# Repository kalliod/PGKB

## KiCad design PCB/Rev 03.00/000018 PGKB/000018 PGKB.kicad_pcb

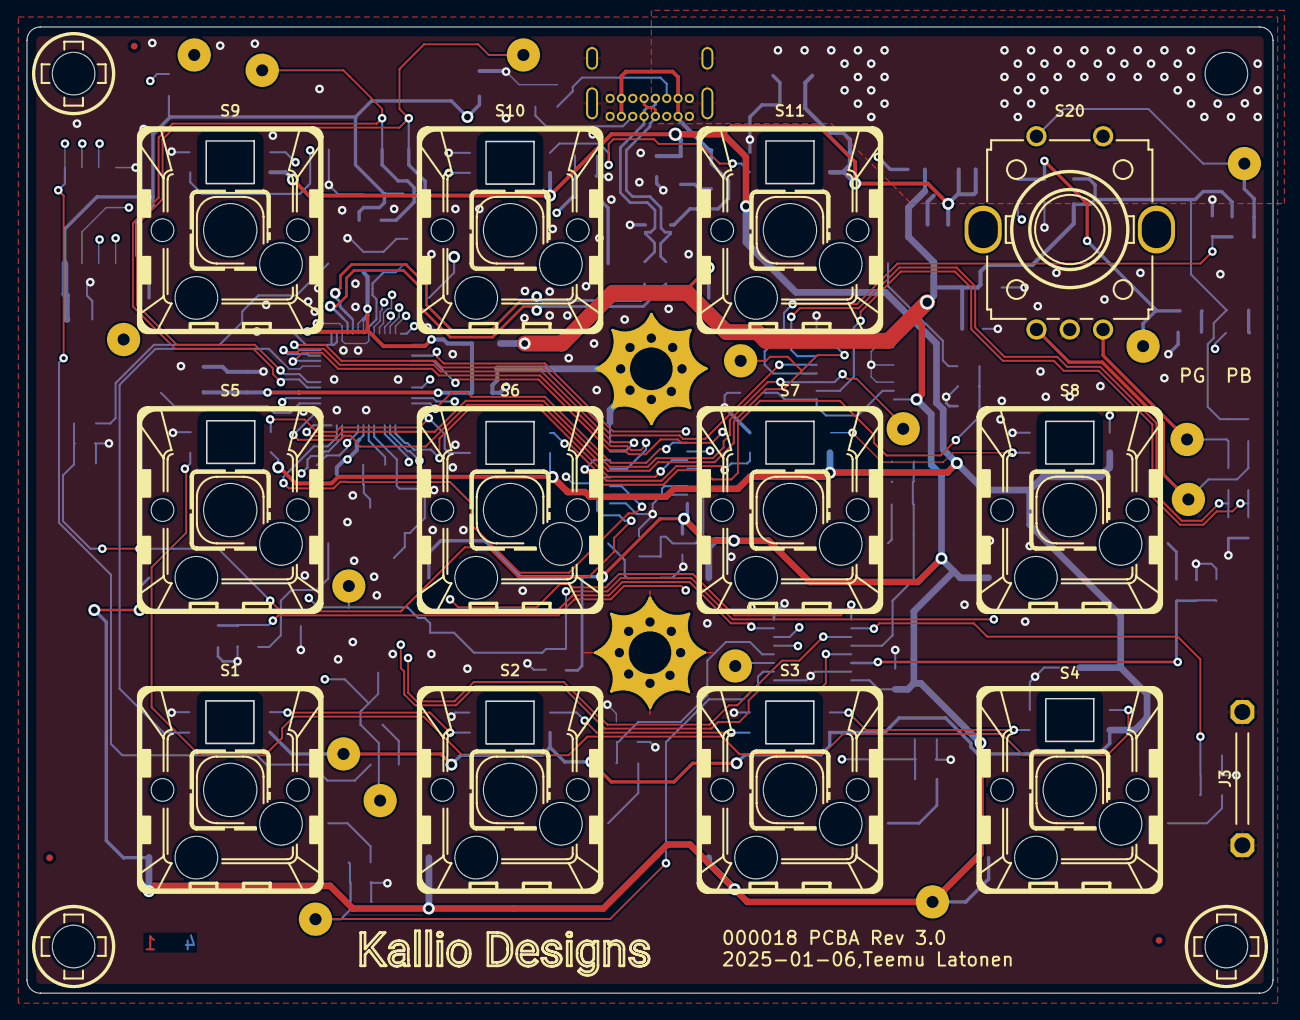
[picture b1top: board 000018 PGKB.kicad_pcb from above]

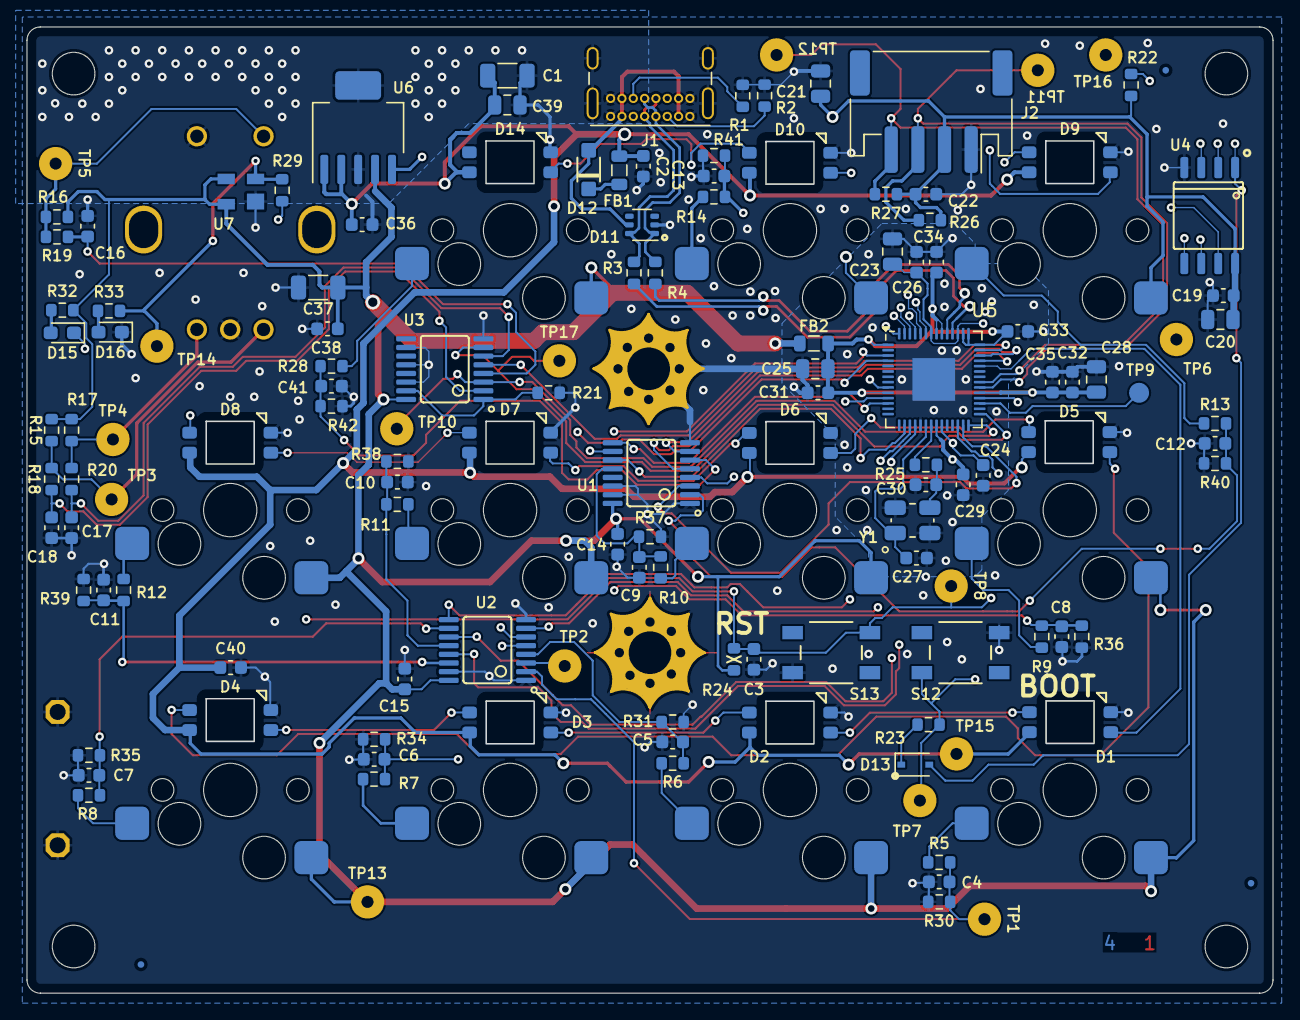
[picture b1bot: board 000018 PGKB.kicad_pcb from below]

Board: 4 copper layers, 93.5 x 72.5 mm, 157 parts (133 on the bottom side), 86 nets.

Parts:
ART1: 4-Layer Marking; ART_4-LAYER
ART2: Logo 2.5 mm Silk; ART_LOGO_TEXT_2.5MM_SILK
C1, C37: 10u; CAPC3216X150N
C2, C14, C15, C16, C17, C18, C19, C22, C24, C26, C29, C31, C32, C33, C34, C35, C36, C38, C40: 100n; CAPC1608X90N
C3, C4, C5, C6, C7, C8, C9, C10, C11, C12, C13, C41: 10n; CAPC1608X90N
C20, C21, C23, C25, C28, C39: 1u; CAPC2012X135N
C27, C30: 27p; CAPC1608X90N
D1, D2, D3, D4, D5, D6, D7, D8, D9, D10, D14: Neopixel Reverse; LEDM_NEO3535_REVERSE_SK6812-E
D11: DRTR5V0U4S-7; SOT-363_SC-70-6
D12: PMEG3010ER,115; DIOC360X180X150N_A
D13: BAT54WS; D_SOD-323
D15: Red; LEDM1608X70M
D16: Green; LEDM1608X70M
FB1, FB2: MMZ2012Y152BT000; INDC2016X100N
FD1, FD2, FD3, FD4, FD5, FD6: Fiducial 0.5 mm; Fiducial_0.5mm_Mask1mm
H1, H2, H4: NPTH 3.2 M3 Clearance; NPTH_3.2mm_M3_clearance
H3: NPTH_3.2; NPTH_3.2mm
H5, H6: PTH 3.2 M3 Clearance; PTH_3.2mm_M3_clearance_B
J1: USB C; USB_C_Receptacle_GCT_USB4085
J2: S4B-PH-SM4-TB; JST_PH_S4B-PH-SM4-TB_1x04-1MP_P2.00mm_Horizontal
J3: GND Hook; GND_HOOK_M
R1, R2, R26, R27: 5k1; RESC1608X55N
R3, R4: 27; RESC1608X55N
R5, R6, R7, R8, R9, R10, R11, R12, R13, R14, R15, R16, R17, R23, R25, R28: 1k; RESC1608X55N
R18, R19, R20, R21, R22, R29: 10k; RESC1608X55N
R24: DNP; RESC1608X55N_DNP
R30, R31, R34, R35, R36, R37, R38, R39, R40, R41, R42: 100k; RESC1608X55N
R32, R33: 360; RESC1608X55N
S1, S2, S3, S4, S5, S6, S7, S8, S9, S10, S11: 4958; SWITCH_BUTTON_Kailh_mx_socket
S12, S13: PTS647SN38SMTR2 LFS; SW_Push_1P1T_NO_CK_PTS647SN50SMTR2LFS
S20: PEC11R-4215K-S0012; RotaryEncoder_Bourns_Vertical_PEC11R-4x15f-Sxxxx
TP1, TP2, TP3, TP4, TP5, TP6, TP7, TP8, TP10, TP11, TP12, TP13, TP14, TP15, TP16, TP17: TP D2.5 mm H0.9mm; TestPoint_Pad_D2.5mm_H0.9mm
TP9: TestPoint_1.5mm_Round; TestPoint_Pad_D1.5mm
U1, U2, U3: SN74HCS365PWR; SOP65P600X150-16N
U4: W25Q80DVSSIG; SOIC127P790X195-8N
U5: RP2040; QFN-56-1EP_7x7mm_P0.4mm_EP3.2x3.2mm
U6: MCP1825T-3302E/DC; SOT127P700X180-6N
U7: CAT811TTBI-GT3; SOT-143_TO-253_M
Y1: 12 MHz; OSCCC320X250X70_M

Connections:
+3V3: C14.1, C15.1, C19.1, C20.1, C21.1, C22.1, C37.1, C38.1, FB2.1, J2.2, R15.1, R16.1, R17.1, R22.1, R24.2, R26.1, R27.1, R32.2, S1.1, S2.1, S3.1, S4.1, S5.1, S6.1, S7.1, S8.1, S9.1, S10.1, S11.1, TP13.1, U1.16 (VCC), U2.16 (VCC), U3.16 (VCC), U4.8 (VCC), U6.4 (VO), U7.3 (~MR), U7.4 (VCC)
/Main/Buttons/Button1: TP2.1, U2.3 (O1), U5.3 (GPIO1)
/Main/Buttons/Button2: U2.5 (O2), U5.4 (GPIO2)
/Main/Buttons/Button3: U2.7 (O3), U5.9 (GPIO7)
/Main/Buttons/Button4: U2.9 (O4), U5.11 (GPIO8)
/Main/Buttons/Button5: U1.9 (O4), U5.12 (GPIO9)
/Main/Buttons/Button6: U1.11 (O5), U5.16 (GPIO13)
/Main/Buttons/Button7: U2.11 (O5), U5.17 (GPIO14)
/Main/Buttons/Button8: U2.13 (O6), U5.18 (GPIO15)
/Main/Buttons/Button9: U1.3 (O1), U5.27 (GPIO16)
/Main/Buttons/Button10: U1.5 (O2), U5.39 (GPIO27_ADC1)
/Main/Buttons/Button11: U1.7 (O3), U5.40 (GPIO28_ADC2)
/Main/Connectors/I2C1_SCL: J2.4, R27.2, TP12.1, U5.35 (GPIO23)
/Main/Connectors/I2C1_SDA: J2.3, R26.2, TP11.1, U5.34 (GPIO22)
/Main/Memory/CLK: U4.6 (CLK), U5.52 (QSPI_SCLK)
/Main/Memory/DATA0: U4.5 (DI(IO0)), U5.53 (QSPI_SD0)
/Main/Memory/DATA1: U4.2 (DO(IO1)), U5.55 (QSPI_SD1)
/Main/Memory/DATA2: U4.3 (~WP(IO2)), U5.54 (QSPI_SD2)
/Main/Memory/DATA3: U4.7 (~HOLD(IO3)), U5.51 (QSPI_SD3)
/Main/Memory/~CS_MEMORY: D13.2 (A), R22.2, U4.1 (~CS), U5.56 (QSPI_SS)
/Main/Microcontroller/1V2: C23.1, C24.1, C26.1, TP6.1, U5.23 (DVDD), U5.45 (VREG_VOUT), U5.50 (DVDD)
/Main/Microcontroller/3V3_MCU: C25.1, C28.1, C29.1, C31.1, C32.1, C33.1, C34.1, C35.1, FB2.2, U5.1 (IOVDD), U5.10 (IOVDD), U5.22 (IOVDD), U5.33 (IOVDD), U5.42 (IOVDD), U5.43 (ADC_AVDD), U5.44 (VREG_IN), U5.48 (USB_VDD), U5.49 (IOVDD)
/Main/Microcontroller/ENC_A: TP10.1, U3.3 (O1), U5.28 (GPIO17)
/Main/Microcontroller/ENC_B: TP17.1, U3.7 (O3), U5.29 (GPIO18)
/Main/Microcontroller/GPIO29: U3.5 (O2), U5.41 (GPIO29_ADC3)
/Main/Microcontroller/NEOPIX_DRIVE: D1.4 (DIN), U5.38 (GPIO26_ADC0)
/Main/Microcontroller/TP10: TP9.1, U5.31 (GPIO20)
/Main/Microcontroller/USBBOOT: R23.2, S12.3, TP7.1, U5.32 (GPIO21)
/Main/Microcontroller/USB_MCU_D_N: R3.2, U5.46 (USB_DM)
/Main/Microcontroller/USB_MCU_D_P: R4.2, U5.47 (USB_DP)
/Main/Microcontroller/~RESET: C3.2, R24.1, R29.2, S13.3, TP8.1, U5.26 (RUN)
/Main/Neopixel LEDs/NEOPIXEL_VDD: C1.1, C2.1, C36.1, C39.1, C40.1, D1.1 (VDD), D2.1 (VDD), D3.1 (VDD), D4.1 (VDD), D5.1 (VDD), D6.1 (VDD), D7.1 (VDD), D8.1 (VDD), D9.1 (VDD), D10.1 (VDD), D14.1 (VDD), FB1.2, TP15.1, U6.1 (~SHDN), U6.2 (VI)
/Main/USB Connector/CC1: J1.A5 (CC1), R2.1
/Main/USB Connector/CC2: J1.B5 (CC2), R1.1
/Main/USB Connector/USB_D_N: D11.6, J1.A7 (D-), J1.B7 (D-), R3.1
/Main/USB Connector/USB_D_P: D11.1, J1.A6 (D+), J1.B6 (D+), R4.1
GND: C1.2, C2.2, C3.1, C4.2, C5.2, C6.2, C7.2, C8.2, C9.2, C10.2, C11.2, C12.2, C13.2, C14.2, C15.2, C16.1, C17.1, C18.1, C19.2, C20.2, C21.2, C22.2, C23.2, C24.2, C25.2, C26.2, C27.2, C28.2, C29.2, C30.2, C31.2, C32.2, C33.2, C34.2, C35.2, C36.2, C37.2, C38.2, C39.2, C40.2, C41.2, D1.3 (VSS), D2.3 (VSS), D3.3 (VSS), D4.3 (VSS), D5.3 (VSS), D6.3 (VSS), D7.3 (VSS), D8.3 (VSS), D9.3 (VSS), D10.3 (VSS), D11.2 (V-), D14.3 (VSS), D16.1 (K), H5.1, H6.1, J1.A1 (GND), J1.A12 (GND), J1.B1 (GND), J1.B12 (GND), J1.S1 (SHIELD), J2.1, J3.1, J3.2 (Pin_1), R1.2, R2.2, R21.1, R30.2, R31.2, R34.2, R35.2, R36.2, R37.2, R38.2, R39.2, R40.2, R41.2, R42.2, S12.2, S13.2, S20.C, S20.S2, U1.1 (E1), U1.8 (GND), U1.14 (I6), U1.15 (E2), U2.1 (E1), U2.8 (GND), U2.15 (E2), U3.8 (GND), U3.10 (I4), U3.12 (I5), U3.14 (I6), U4.4 (GND), U5.19 (TESTEN), U5.57 (GND), U6.3 (GND), U6.6 (GND), U7.1 (GND), Y1.2 (GND), Y1.4 (GND)
unnamed: C30.1, R25.1, Y1.3
unnamed: D1.2 (DOUT), D2.4 (DIN)
unnamed: D2.2 (DOUT), D3.4 (DIN)
unnamed: D3.2 (DOUT), D4.4 (DIN)
unnamed: D4.2 (DOUT), D5.4 (DIN)
unnamed: D5.2 (DOUT), D6.4 (DIN)
unnamed: D6.2 (DOUT), D7.4 (DIN)
unnamed: D7.2 (DOUT), D8.4 (DIN)
unnamed: D8.2 (DOUT), D9.4 (DIN)
unnamed: D9.2 (DOUT), D10.4 (DIN), TP16.1
unnamed: D10.2 (DOUT), D14.4 (DIN)
unnamed: D11.5 (V+), D12.2 (A), J1.A4 (VBUS), J1.A9 (VBUS), J1.B4 (VBUS), J1.B9 (VBUS)
unnamed: D12.1 (K), FB1.1
unnamed: D13.1 (K), R23.1
unnamed: D15.2 (A), R32.1
unnamed: D15.1 (K), U6.5 (PG)
unnamed: D16.2 (A), R33.1
unnamed: R5.1, S1.2
unnamed: R6.1, S2.2
unnamed: R7.1, S3.2
unnamed: R8.1, S4.2
unnamed: R9.1, S5.2
unnamed: R10.1, S6.2
unnamed: R11.1, S7.2
unnamed: R12.1, S8.2
unnamed: R13.1, S9.2
unnamed: R14.1, S10.2
unnamed: R15.2, R18.1, S20.A, TP3.1
unnamed: R16.2, R19.1, S20.S1, TP5.1
unnamed: R17.2, R20.1, S20.B, TP4.1
unnamed: R28.1, S11.2
unnamed: C12.1, R13.2, R40.1, U1.2 (I1)
unnamed: C13.1, R14.2, R41.1, U1.4 (I2)
unnamed: C41.1, R28.2, R42.1, U1.6 (I3)
unnamed: C8.1, R9.2, R36.1, U1.10 (I4)
unnamed: C9.1, R10.2, R37.1, U1.12 (I5)
unnamed: C4.1, R5.2, R30.1, TP1.1, U2.2 (I1)
unnamed: C5.1, R6.2, R31.1, U2.4 (I2)
unnamed: C6.1, R7.2, R34.1, U2.6 (I3)
unnamed: C7.1, R8.2, R35.1, U2.10 (I4)
unnamed: C10.1, R11.2, R38.1, U2.12 (I5)
unnamed: C11.1, R12.2, R39.1, U2.14 (I6)
unnamed: R21.2, U3.1 (E1), U3.15 (E2)
unnamed: C18.2, R18.2, U3.2 (I1)
unnamed: C16.2, R19.2, U3.4 (I2)
unnamed: C17.2, R20.2, U3.6 (I3)
unnamed: C27.1, U5.20 (XIN), Y1.1
unnamed: R25.2, U5.21 (XOUT)
PERIP_~RESET: R29.1, R33.2, TP14.1, U7.2 (RST)

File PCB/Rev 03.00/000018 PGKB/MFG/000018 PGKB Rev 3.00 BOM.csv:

Reference,Value,Datasheet,Qty,DNP,DNP,MFG_PartNo,Manufacturer,Supplier,Supplier_PartNo
"C1,C37",10u,https://www.samsungsem.com/kr/support/product-search/mlcc/CL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,2,F,F,CL31B106MOHNNNE,Samsung Electro-Mechanics,Digi-Key,1276-6641-1-ND
"C2,C14,C15,C16,C17,C18,C19,C22,C24,C26,C29,C31,C32,C33,C34,C35,C36,C38,C40",100n,https://mm.digikey.com/Volume0/opasdata/d220001/medias/docus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,19,F,F,CL10B104KB8NNWC,Samsung,Digi-Key,1276-1935-1-ND
"C3,C4,C5,C6,C7,C8,C9,C10,C11,C12,C13,C41",10n,https://product.tdk.com/en/system/files?file=dam/doc/product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,12,F,F,C1608X7R2A103K080AA,TDK Corporation,Digi-Key,445-1304-1-ND
"C20,C21,C23,C25,C28,C39",1u,https://mm.digikey.com/Volume0/opasdata/d220001/medias/docus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,6,F,F,CL21B105KAFNNNE,Samsung Electro-Mechanics,Digi-Key,1276-1066-1-ND
"C27,C30",27p,http://www.passivecomponent.com/wp-content/uploads/datasheet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,2,F,F,0603N270J500CT,Walsin Technology Corporation,Digi-Key,1292-1511-1-ND
"D1,D2,D3,D4,D5,D6,D7,D8,D9,D10,D14",Neopixel Reverse,https://cdn-shop.adafruit.com/product-files/4960/4960_SK6812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,11,F,F,4960,Adafruit Industries LLC,Digi-Key,1528-4960-ND
D11,TVS_5V5_DRTR5V0U4S-7-M,https://www.diodes.com/assets/Datasheets/DRTR5V0U4S.pdf,1,F,F,DRTR5V0U4S-7,Diodes Incorporated,Digi-Key,DRTR5V0U4S-7DICT-ND
D12,Schottky_30V_1A_PMEG3010ER_115,https://assets.nexperia.com/documents/data-sheet/PMEG3010ER.pdf,1,F,F,"PMEG3010ER,115",Nexperia USA Inc.,Digi-Key,1727-5201-1-ND
D13,Schottky_30V_200mA_DCo_BAT54WS,https://diotec.com/tl_files/diotec/files/pdf/datasheets/bat54ws.pdf,1,F,F,BAT54WS,DComponents,Digi-Key,2721-BAT54WSTR-ND
D15,Red,https://mm.digikey.com/Volume0/opasdata/d220001/medias/docus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,1,F,F,B1911USD-20D000114U1930,Harvatek Corporation,Digi-Key,3147-B1911USD-20D000114U1930CT-ND
D16,Green,https://mm.digikey.com/Volume0/opasdata/d220001/medias/docus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,1,F,F,B1911NG--20D000214U1930,Harvatek Corporation,Digi-Key,3147-B1911NG--20D000214U1930CT-ND
"FB1,FB2",MMZ2012Y152BT000,https://product.tdk.com/en/system/files?file=dam/doc/product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,2,F,F,MMZ2012Y152BT000,Abracon LLC,Digi-Key,445-MMZ2012Y152BT000CT-ND
"H1,H2,H4",NPTH 3.2 M3 Clearance,,3,T,T,DNP,DNP,DNP,DNP
H3,NPTH_3.2,,1,T,T,DNP,DNP,DNP,DNP
"H5,H6",PTH 3.2 M3 Clearance,,2,T,T,DNP,DNP,DNP,DNP
J1,USB C,https://gct.co/files/drawings/usb4085.pdf,1,F,F,USB4085-GF-A,GCT,Digi-Key,2073-USB4085-GF-ACT-ND
J2,S4B-PH-SM4-TB,https://www.jst-mfg.com/product/pdf/eng/ePH.pdf,1,F,F,S4B-PH-SM4-TB,JST Sales America Inc.,Digi-Key,455-S4B-PH-SM4-TBCT-ND
J3,GND Hook,,1,T,T,DNP,DNP,DNP,DNP
"R1,R2,R26,R27",R_0603_5100_1%,https://www.seielect.com/catalog/sei-rmcf_rmcp.pdf,4,F,F,RMCF0603JT5K10,Stackpole Electronics Inc,Digi-Key,RMCF0603JT5K10CT-ND
"R3,R4",27,https://www.bourns.com/docs/product-datasheets/cr.pdf?sfvrsn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,2,F,F,CR0603-FX-27R0ELF,Bourns Inc.,Digi-Key,CR0603-FX-27R0ELFCT-ND
"R5,R6,R7,R8,R9,R10,R11,R12,R13,R14,R15,R16,R17,R23,R25,R28",1k,https://www.seielect.com/Catalog/SEI-RMCF_RMCP.pdf,16,F,F,RMCF0603JT1K00,Stackpole Electronics Inc,Digi-Key,RMCF0603JT1K00CT-ND
"R18,R19,R20,R21,R22,R29",10k,https://www.seielect.com/Catalog/SEI-RMCF_RMCP.pdf,6,F,F,RMCF0603FT10K0,Stackpole Electronics Inc,Digi-Key,RMCF0603FT10K0CT-ND
R24,R_0603_DNP,,1,T,T,DNP,DNP,DNP,DNP
"R30,R31,R34,R35,R36,R37,R38,R39,R40,R41,R42",100k,https://www.seielect.com/catalog/sei-rmcf_rmcp.pdf,11,F,F,RMCF0603FT100K,Stackpole Electronics Inc,Digi-Key,RMCF0603FT100KCT-ND
"R32,R33",360,https://www.yageo.com/upload/media/product/productsearch/dat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,2,F,F,RT0603FRE07360RL,YAGEO,Digi-Key,13-RT0603FRE07360RLCT-ND
"S1,S2,S3,S4,S5,S6,S7,S8,S9,S10,S11",4958,https://mm.digikey.com/Volume0/opasdata/d220001/medias/docus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,11,F,F,4958,Adafruit,Digi-Key,1528-4958-ND
"S12,S13",4.30181E+11,https://www.mouser.fi/datasheet/2/445/430181038816-1717160.pdf,2,F,F,4.30181E+11,Wurth Elektronik,Mouser,710-430181038816
S20,PEC11R-4215K-S0012,https://www.bourns.com/docs/Product-Datasheets/PEC11R.pdf,1,F,F,PEC11R-4215K-S0012,Bourns Inc.,Digi-Key,PEC11R-4215K-S0012-ND
"TP1,TP2,TP3,TP4,TP5,TP6,TP7,TP8,TP10,TP11,TP12,TP13,TP14,TP15,TP16,TP17",TP D2.5 mm H0.9mm,DNP,16,T,T,DNP,DNP,DNP,DNP
TP9,TestPoint_1.5mm_Round,DNP,1,T,T,DNP,DNP,DNP,DNP
"U1,U2,U3",SN74HCS365PWR,https://www.ti.com/lit/ds/symlink/sn74hcs365.pdf,3,F,F,SN74HCS365PWR,Texas Instruments,Digi-Key,296-SN74HCS365PWRCT-ND
U4,W25Q80DVSSIG,https://www.winbond.com/resource-files/w25q80dv%20dl_revh_10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,1,F,F,W25Q80DVSSIG,Winbond Electronics,Digi-Key,W25Q80DVSSIG-ND
U5,RP2040,https://datasheets.raspberrypi.com/rp2040/rp2040-datasheet.pdf,1,F,F,SC0914(13),Raspberry Pi,Digi-Key,2648-SC0914(13)CT-ND
U6,MCP1825T-3302E/DC,https://ww1.microchip.com/downloads/en/DeviceDoc/22056b.pdf,1,F,F,MCP1825T-3302E/DC,Microchip Technology,Digi-Key,MCP1825T-3302E/DCCT-ND
U7,CAT811TTBI-GT3,https://www.onsemi.com/pdf/datasheet/cat811-d.pdf,1,F,F,CAT811TTBI-GT3,onsemi,Digi-Key,CAT811TTBI-GT3OSCT-ND
Y1,12 MHz,https://www.mouser.fi/datasheet/2/3/ABM8_272_T3-3392615.pdf,1,F,F,ABM8-272-T3,Abracon LLC,Digi-Key,535-ABM8-272-T3CT-ND

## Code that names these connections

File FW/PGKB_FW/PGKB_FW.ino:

#include <Wire.h>
#include "Adafruit_MCP23017.h"
#include "KD_ardu_button.h"
#include <Keyboard.h>

/* Hardware configuration */

// TL: My keyboard writes 900 characters if a key is pressed for 30 sec. If
// two keys are pressed the amount of characters is doubled

// HW
#define BUTTON_DEBOUNCE 20                          // button debounce (ms)
#define NO_OF_BUTTONS 8

// ADC
#define AUX_VREF 2.56
#define ADC_CHANNELS 1024

/* Define debugging level */

// Doesn't work too well with serial port and HID enabled
#define DEBUG_LEVEL 0
#define POST_INTERVAL 5000

/* Serial port */

#define SERIAL_BAUD_RATE 57600                      // 57600 max with internal 8 MHz oscillator

/* Keyboard layout */

#define KB_LAYOUT_FI

/***********************************************************************************************************************/
/*                                                  pin definitions                                                    */
/***********************************************************************************************************************/

/* Arduino digital */
const int button1_pin = 12;
const int button2_pin = 6;
const int button3_pin = 8;
const int button4_pin = 0;   // NOT CONNECTED IN PCB REV 1.00
const int button5_pin = 9;
const int button6_pin = 10;
const int button7_pin = 11;
const int button8_pin = 13;

const int interrupt7_pin = 7;

//const int rx_led_pin = ??; // ARE THESE HW FUNCTIONS?
//const int tx_led_pin = 4;

/* Arduino analog */
const int analog0 = 14;
const int analog1 = 15;
//const int analog2 = 16;     // NOT IN USE
//const int analog3 = 17;     // NOT IN USE
const int analog4 = 18;
const int analog5 = 19;
//const int analog6 = 20;     // WHICH PIN?
//const int analog7 = 21;     // WHICH PIN?

/***********************************************************************************************************************/
/*                                                   VARIABLES                                                         */
/***********************************************************************************************************************/

/* Other variables */

// pin, pullup, inverted
Button onb_button[NO_OF_BUTTONS];

// Debugging
unsigned long _last_post_time = 0;
byte cycle_count = 0;

// Keyboard
bool b_pressed[NO_OF_BUTTONS];
char b_char[NO_OF_BUTTONS][2];

/***********************************************************************************************************************/
/*                                                   FUNCTIONS                                                         */
/***********************************************************************************************************************/

/* Analog in */
float read_voltage();

/***********************************************************************************************************************/
/*                                                   SETUP LOOP                                                        */
/***********************************************************************************************************************/

void setup() {

/* Keyboard layout */
// compare to US Apple Macintosh keyboard layout

#ifdef KB_LAYOUT_US
  b_char[0][0] = '\0';
  b_char[0][1] = ')';
  b_char[1][0] = '\0';
  b_char[1][1] = '(';
  b_char[2][0] = '\0';
  b_char[2][1] = '}';
  b_char[3][0] = '\0';
  b_char[3][1] = '{';
  b_char[4][0] = '\0';
  b_char[4][1] = ']';
  b_char[5][0] = '\0';
  b_char[5][1] = '[';
  b_char[6][0] = '\0';
  b_char[6][1] = '"';
  b_char[7][0] = '\0';
  b_char[7][1] = '\'';
#endif

#ifdef KB_LAYOUT_FI
  b_char[0][0] = KEY_LEFT_SHIFT;
  b_char[0][1] = '9';
  b_char[1][0] = KEY_LEFT_SHIFT;
  b_char[1][1] = '8';
  b_char[2][0] = KEY_RIGHT_ALT;
  b_char[2][1] = '0';
  b_char[3][0] = KEY_RIGHT_ALT;
  b_char[3][1] = '7';
  b_char[4][0] = KEY_RIGHT_ALT;
  b_char[4][1] = '9';
  b_char[5][0] = KEY_RIGHT_ALT;
  b_char[5][1] = '8';
  b_char[6][0] = KEY_LEFT_SHIFT;
  b_char[6][1] = '2';
  b_char[7][0] = '\0';
  b_char[7][1] = '\\';
#endif

  // ADC
  analogReference(INTERNAL);

  /* Pin settings on Arduino */

  // pins
  pinMode(interrupt7_pin, INPUT_PULLUP);

  onb_button[0].setPin(button1_pin);
  onb_button[1].setPin(button2_pin);
  onb_button[2].setPin(button3_pin);
  onb_button[3].setPin(button4_pin);
  onb_button[4].setPin(button5_pin);
  onb_button[5].setPin(button6_pin);
  onb_button[6].setPin(button7_pin);
  onb_button[7].setPin(button8_pin);
  
  for (int i = 0; i < NO_OF_BUTTONS; i++){
    b_pressed[i] = false;
  }

  for (int i = 0; i < NO_OF_BUTTONS; i++){
    onb_button[i].setPullup(HIGH);
    onb_button[i].setInverted(HIGH);
  }

  // Keyboard
  Keyboard.begin();

  /* Serial communications setup */
#if DEBUG_LEVEL > 1
  Serial.begin(SERIAL_BAUD_RATE);
  while(!Serial){
    ;                                               // Needed for Atmega32U4
  }  
#endif

#if DEBUG_LEVEL > 1
  Serial.println(F("Serial port opened"));
  Serial.print(F("Serial baud rate: "));
  Serial.print(SERIAL_BAUD_RATE);
  Serial.println(F(" bit/s"));
#endif

  /* Setup complete */

#if DEBUG_LEVEL > 1
  Serial.println(F("Setup complete"));
#endif
  
}

/***********************************************************************************************************************/
/*                                                   MAIN LOOP                                                         */
/***********************************************************************************************************************/

void loop() {

  for (int i = 0; i < 8; i++) {
    if (onb_button[i].pressed()) {
      delay(BUTTON_DEBOUNCE);
      if(onb_button[i].state()) {
#if DEBUG_LEVEL > 3
        Serial.print(F("pressed key: "));
        Serial.println(i+1);
#endif
        for (int j = 0; j < 2; j++) {
          Keyboard.press(b_char[i][j]);
        }
        b_pressed[i] = true;
      }

    } else if (b_pressed[i] && onb_button[i].isReleased()) {
      delay(BUTTON_DEBOUNCE);
      b_pressed[i] = false;
#if DEBUG_LEVEL > 3
      Serial.print(F("released key: "));
      Serial.println(i+1);
#endif
      Keyboard.releaseAll();
    }
  }

// Debugging
#if DEBUG_LEVEL > 6
    if((_last_post_time + POST_INTERVAL) < millis())
    {
      // Debug info
      Serial.println(F("debugging info:"));
      Serial.print(F("Cycle: "));
      Serial.println(cycle_count);

      _last_post_time = millis();
      cycle_count++;
      Serial.println("------");
  }
#endif
} // void loop()

/* Analog in */
float read_voltage() {
  float _result = 0;
  _result = AUX_VREF * analogRead(A1) / ADC_CHANNELS;
  return _result;
}

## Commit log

2019-04-06 Import libraries
2019-04-06 Initial
2019-04-06 First tests
    Works fine for two keys
2019-04-06 Country variants and buttons as array
    Can't really use modifier keys
2019-04-06 Added modifier keys
    Worked fine for a while, but started to give 9 presses at once
2019-04-06 Bugfix
    All good again Finnish layout defined
2023-10-08 Rev 2 schematic started
2023-10-08 buttons
2023-10-08 cleanup
2023-10-12 schematic
2023-10-15 ledit
2023-10-15 skema
2023-10-16 Layout
2023-10-17 Board outline update
2023-10-17 step
2023-10-17 sitte vaan routaus
2023-10-17 4L board
2023-10-18 Leiskaa
2023-10-19 error fixing
2023-10-20 päivityksiä
2023-10-22 Review checklists
2023-10-23 USB connector moved
2023-10-27 Button support
2023-10-27 PN added
2024-01-24 mfg files
2024-01-24 MODIFICATIONS To Rev 2
2024-01-24 MODIFICATIONS Updates
2024-02-03 RPi keyboard FW
2024-02-10 file rename
2024-04-08 Updates started
2024-05-04 Maybe new psu needed
2024-07-14 Bugfixes for Rev 2
    Oscillator, USB reversed, USB series resistors values
2024-07-14 File version update
2024-07-14 Update USBcon.kicad_sch
    Changed back to 0603 components
2024-07-14 Updated layout from schematic
2024-07-14 routed all
2024-07-14 Resolved DRC problems
2024-07-15 Test points for encoder signals
2024-07-15 Update PKGBV2.ino
    Ehkä tän pitäis toimia paremmin näin?
2024-07-15 Encoder Test points to layout
2024-07-16 Signals renamed
2024-07-16 Nappi- ja neopixel-testausta
2024-07-16 GND hook added
2024-08-18 Rev3 outputs
2024-08-26 STL generated
2024-08-26 update stl
2024-11-11 SW updates
2025-01-06 Rev 3 tekemista
2025-01-08 mfg outputs
